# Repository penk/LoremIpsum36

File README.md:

## LoremIpsum36 - A minimal Gateron LP column staggered keyboard

## Bill of Materials (BOM)

Quantity | Item
--- | ---
1 | RP2040-Zero
1 | LoremIpsum36 PCB
36 | Gateron LP switches and keycaps 
36 | KS-33 sockets
36 | 1N4148SOD-123 diodes
1 | LoremIpsum36 case
10 | M2×3 heat-set threaded inserts
10 | M2×12 countersunk screws

## Production Files

To place an order for the LoremIpsum36 PCB:

- Use the Gerber files available in the [production/](production/) folder.
- The [BOM](production/BOM.csv) and [CPL](production/CPL.csv) files can be used with a PCBA service -- especially if you prefer to avoid soldering small diodes.

All components (except the MCU) are soldered to the **back (bottom)** side of the board.

> [!CAUTION]
> To maintain the low profile of the board, the MCU (RP2040-Zero) must be soldered **on the front (top)** side of the PCB, with its components facing **downwards**. 

The boot/reset button should face the bottom side of the keyboard. Double-check alignment before soldering to avoid incorrect placement: 

The complete PCB design project is available in the [kicad/](kicad/) folder.

## 3D Printable Files

Print the `loremipsum36-top` and `loremipsum36-bottom` case using the provided [STL files](case/), along with the threaded inserts and M2 screws.  

If you prefer to use the keyboard without a case, you will need to print the plate `loremipsum36-plate`, or laser cut a plate using the provided DXF file.

## Firmware

Precompiled VIA-enabled firmware:

- Flash `penk_loremipsum36_default.uf2` under [firmware/](firmware/) to the RP2040 MCU.
- Load the [via.json](firmware/QMK/keyboards/penk/loremipsum36/via.json) file in the `Design` tab for [VIA](https://usevia.app) configuration.

The QMK source is available under [firmware/QMK/keyboards/penk/loremipsum36](firmware/QMK/keyboards/penk/loremipsum36/).

### Default Keymaps 

The keymap is based on Rico's [rsta layout](https://github.com/rstacruz/my_qmk_keymaps/blob/main/preview.png), and the custom keycaps are made by FK Keycaps. 

You can order the same keycap set or customize yours at [https://fkcaps.com/custom/D7829J](https://fkcaps.com/custom/D7829J).

## Copyright and License
Copyright (c) 2025 Penk Chen. All rights reserved.

All files are licensed under the MIT license. For more information, see the [LICENSE](LICENSE).

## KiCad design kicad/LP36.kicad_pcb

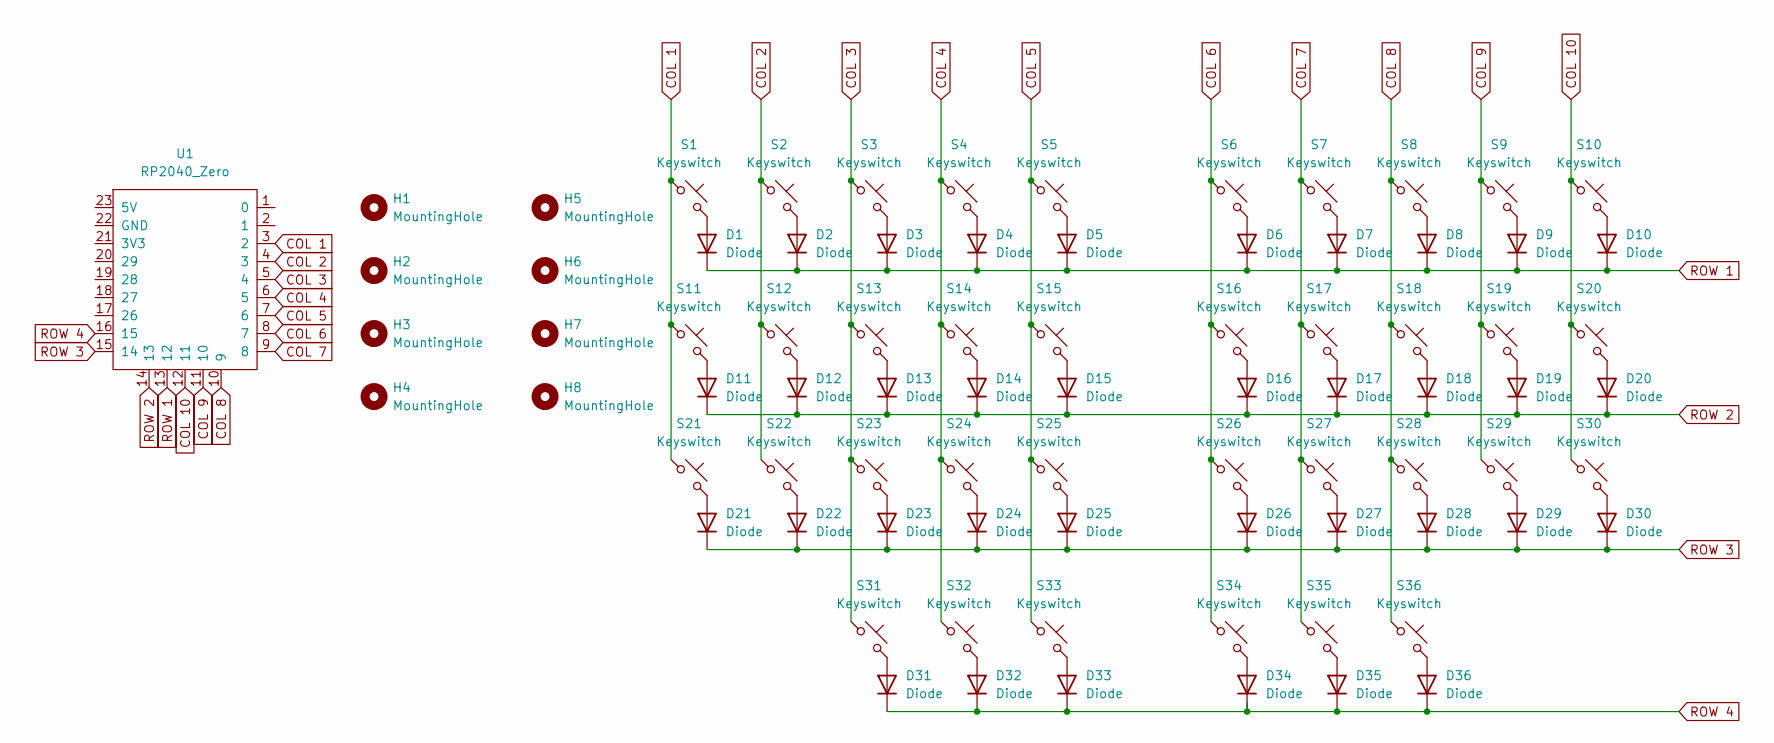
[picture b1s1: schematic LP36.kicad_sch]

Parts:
D1, D2, D3, D4, D5, D6, D7, D8, D9, D10, D11, D12, D13, D14, D15, D16, D17, D18, D19, D20, D21, D22, D23, D24, D25, D26, D27, D28, D29, D30, D31, D32, D33, D34, D35, D36: Diode; Diode_SOD-123
H1, H2, H3, H4, H5, H6, H7, H8: MountingHole; MountingHole_2.2mm_M2
S1, S2, S3, S4, S5, S6, S7, S8, S9, S10, S11, S12, S13, S14, S15, S16, S17, S18, S19, S20, S21, S22, S23, S24, S25, S26, S27, S28, S29, S30, S31, S32, S33, S34, S35, S36: Keyswitch; SW_KS33_HS_KS-2P02B01-02_HS_1u
U1: RP2040_Zero; RP2040_Zero_holes

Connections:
COL 1: S1.1, S11.1, S21.1, U1.3 (2)
COL 2: S2.1, S12.1, S22.1, U1.4 (3)
COL 3: S3.1, S13.1, S23.1, S31.1, U1.5 (4)
COL 4: S4.1, S14.1, S24.1, S32.1, U1.6 (5)
COL 5: S5.1, S15.1, S25.1, S33.1, U1.7 (6)
COL 6: S6.1, S16.1, S26.1, S34.1, U1.8 (7)
COL 7: S7.1, S17.1, S27.1, S35.1, U1.9 (8)
COL 8: S8.1, S18.1, S28.1, S36.1, U1.10 (9)
COL 9: S9.1, S19.1, S29.1, U1.11 (10)
COL 10: S10.1, S20.1, S30.1, U1.12 (11)
unnamed: D1.2 (A), S1.2
unnamed: D2.2 (A), S2.2
unnamed: D3.2 (A), S3.2
unnamed: D4.2 (A), S4.2
unnamed: D5.2 (A), S5.2
unnamed: D6.2 (A), S6.2
unnamed: D7.2 (A), S7.2
unnamed: D8.2 (A), S8.2
unnamed: D9.2 (A), S9.2
unnamed: D10.2 (A), S10.2
unnamed: D11.2 (A), S11.2
unnamed: D12.2 (A), S12.2
unnamed: D13.2 (A), S13.2
unnamed: D14.2 (A), S14.2
unnamed: D15.2 (A), S15.2
unnamed: D16.2 (A), S16.2
unnamed: D17.2 (A), S17.2
unnamed: D18.2 (A), S18.2
unnamed: D19.2 (A), S19.2
unnamed: D20.2 (A), S20.2
unnamed: D21.2 (A), S21.2
unnamed: D22.2 (A), S22.2
unnamed: D23.2 (A), S23.2
unnamed: D24.2 (A), S24.2
unnamed: D25.2 (A), S25.2
unnamed: D26.2 (A), S26.2
unnamed: D27.2 (A), S27.2
unnamed: D28.2 (A), S28.2
unnamed: D29.2 (A), S29.2
unnamed: D30.2 (A), S30.2
unnamed: D31.2 (A), S31.2
unnamed: D32.2 (A), S32.2
unnamed: D33.2 (A), S33.2
unnamed: D34.2 (A), S34.2
unnamed: D35.2 (A), S35.2
unnamed: D36.2 (A), S36.2
ROW 1: D1.1 (K), D2.1 (K), D3.1 (K), D4.1 (K), D5.1 (K), D6.1 (K), D7.1 (K), D8.1 (K), D9.1 (K), D10.1 (K), U1.13 (12)
ROW 2: D11.1 (K), D12.1 (K), D13.1 (K), D14.1 (K), D15.1 (K), D16.1 (K), D17.1 (K), D18.1 (K), D19.1 (K), D20.1 (K), U1.14 (13)
ROW 3: D21.1 (K), D22.1 (K), D23.1 (K), D24.1 (K), D25.1 (K), D26.1 (K), D27.1 (K), D28.1 (K), D29.1 (K), D30.1 (K), U1.15 (14)
ROW 4: D31.1 (K), D32.1 (K), D33.1 (K), D34.1 (K), D35.1 (K), D36.1 (K), U1.16 (15)

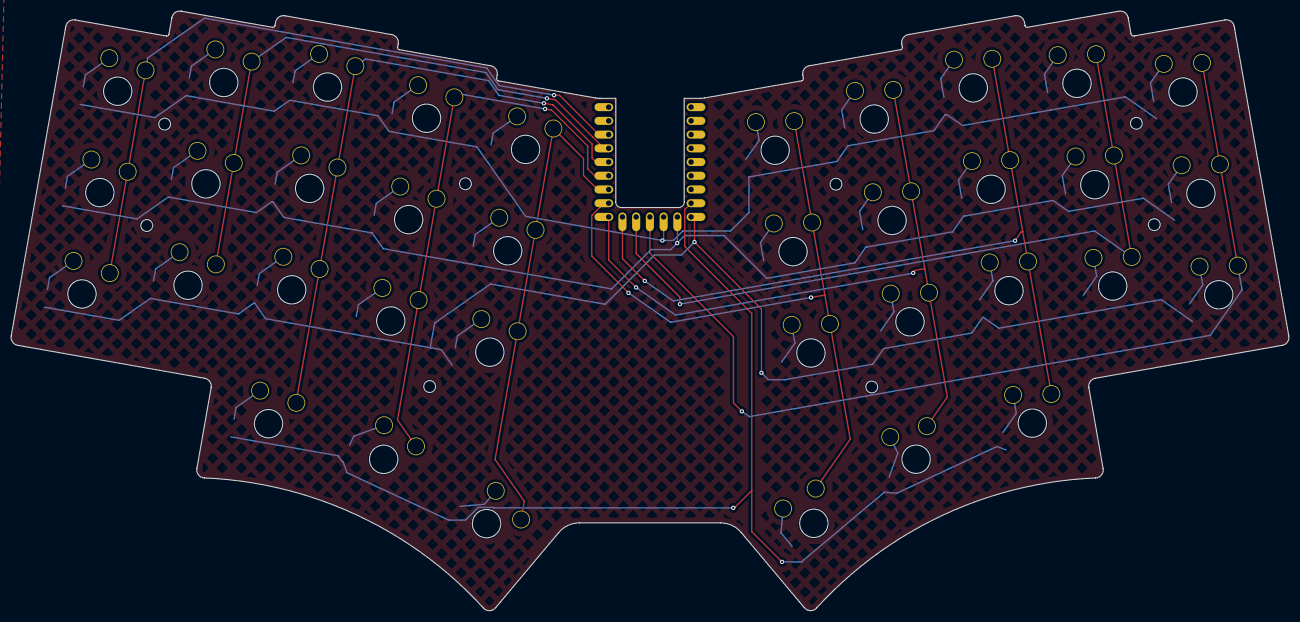
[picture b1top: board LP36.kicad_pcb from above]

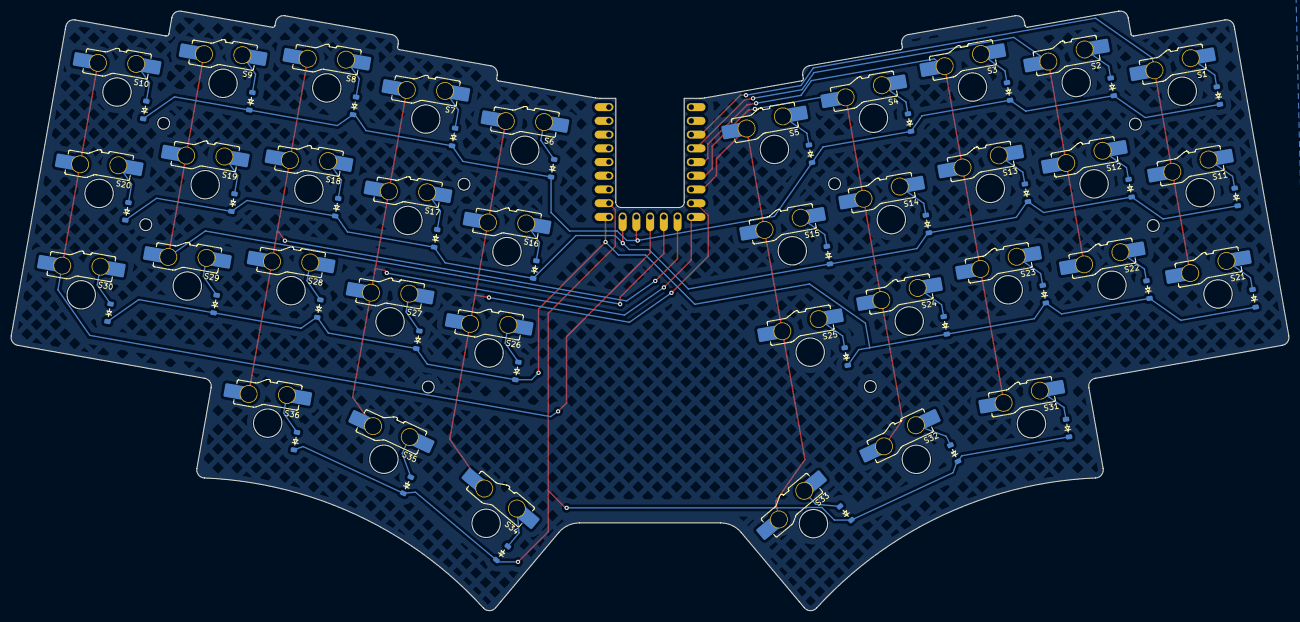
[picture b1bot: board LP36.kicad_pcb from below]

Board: 2 copper layers, 236.5 x 111.0 mm, 81 parts (73 on the bottom side), 50 nets.

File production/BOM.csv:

Designator,Footprint,Quantity,Value,LCSC Part #
"D1, D10, D11, D12, D13, D14, D15, D16, D17, D18, D19, D2, D20, D21, D22, D23, D24, D25, D26, D27, D28, D29, D3, D30, D31, D32, D33, D34, D35, D36, D4, D5, D6, D7, D8, D9",Diode_SOD-123,36,Diode,C2972760
"S1, S10, S11, S12, S13, S14, S15, S16, S17, S18, S19, S2, S20, S21, S22, S23, S24, S25, S26, S27, S28, S29, S3, S30, S31, S32, S33, S34, S35, S36, S4, S5, S6, S7, S8, S9",SW_KS33_HS_KS-2P02B01-02_HS_1u,36,Keyswitch,C9900059694

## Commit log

2025-02-04 Add STEP and DXF for the case
2025-02-05 Add plate
